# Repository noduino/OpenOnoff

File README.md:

Noduino Open Onoff
=======================================

[*Noduino Open Onoff (OpenOnoff V1.0)*](http://wiki.jackslab.org/Noduino_OpenOnoff)

[*Noduino Open Onoff (OpenOnoff V1.0)*](http://wiki.jackslab.org/Noduino_OpenOnoff)

Overview
-------------------

* AC 85V - 250V WiFi Smart Switch
* ESP8285 inside
* 250V 10A relay
* Shell size 63mm x 33mm x 21mm (H)

Shell
-------------------

* https://item.taobao.com/item.htm?id=535597515580

WiFi Module
-------------------

[*Noduino NodeC WiFi Module*](http://wiki.jackslab.org/Noduino_SmartNode)

SCH
-------------------

[*Noduino Open Onoff (OpenOnoff V1.0)*](http://wiki.jackslab.org/Noduino_OpenOnoff)

Layout
-------------------

[*Noduino Open Onoff (OpenOnoff V1.0)*](http://wiki.jackslab.org/Noduino_OpenOnoff)

WiKi
-------------------

* http://wiki.jackslab.org/Noduino_OpenOnoff

License Information
-------------------
The hardware is released under [Creative Commons ShareAlike 4.0 International](https://creativecommons.org/licenses/by-sa/4.0/).

Distributed as-is; no warranty is given.

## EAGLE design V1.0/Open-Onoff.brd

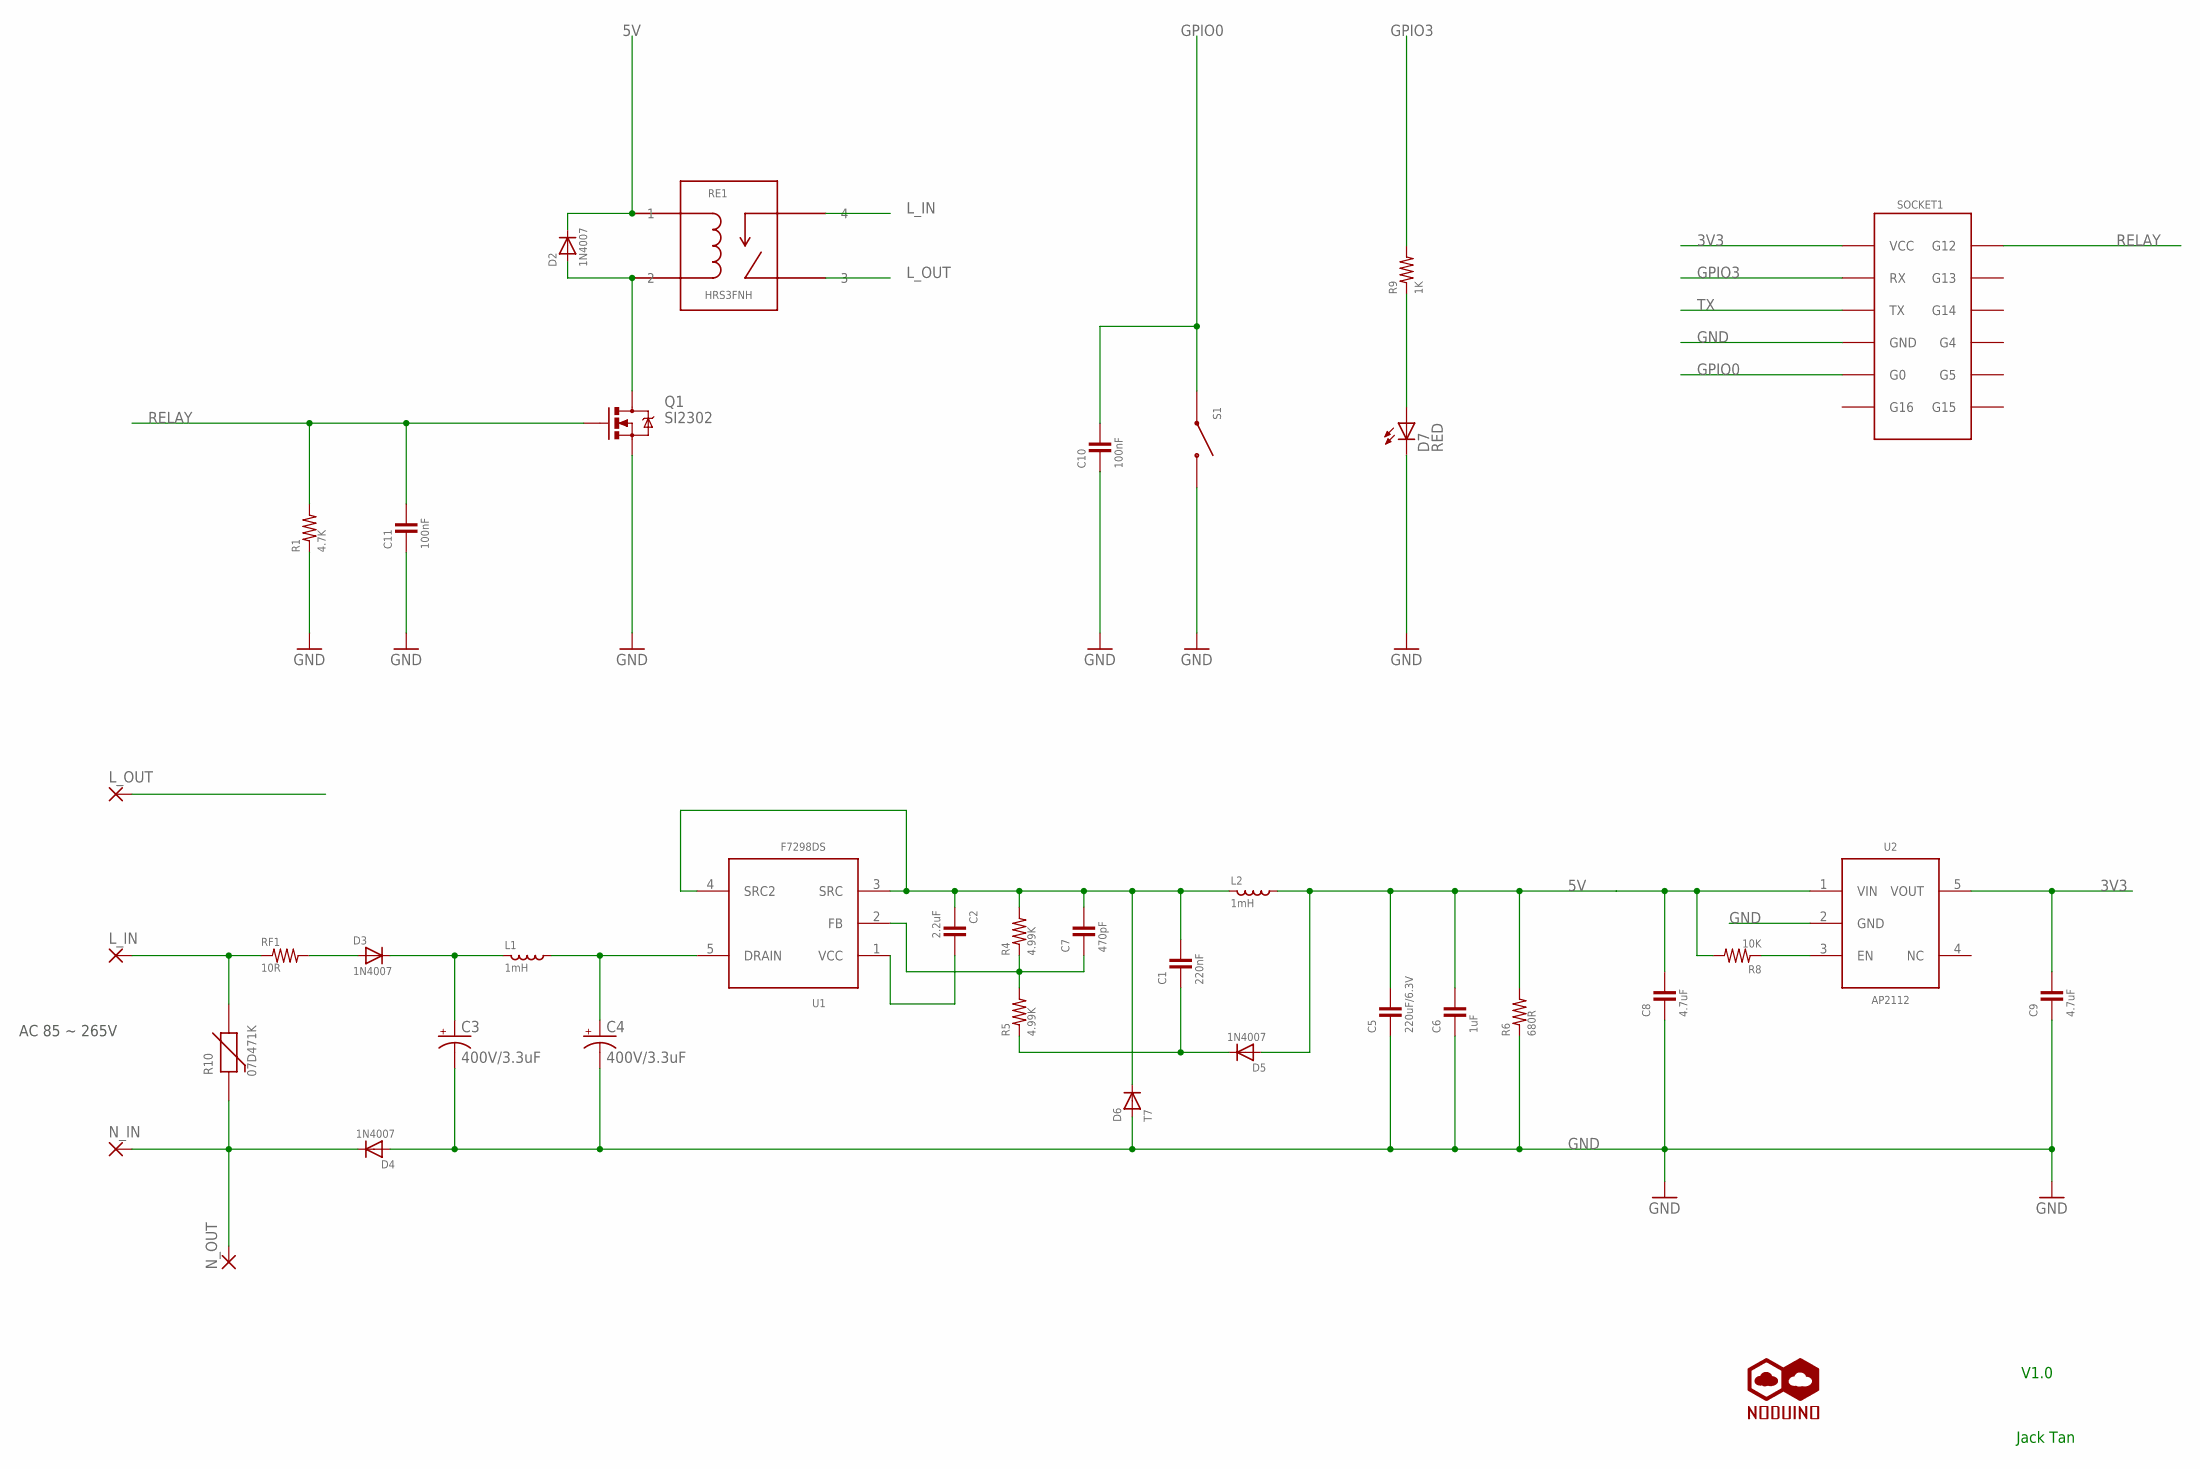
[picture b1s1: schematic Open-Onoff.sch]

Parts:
C1: 220nF; 0402-CAP
C2: 2.2uF; 0603-CAP
C3, C4: 400V/3.3uF; CPOL-RADIOA-3.3UF-400V
C5: 220uF/6.3V; B3528-CAP
C6: 1uF; 0402-CAP
C7: 470pF; 0402-CAP
C8, C9: 4.7uF; 0603-CAP
C10, C11: 100nF; 0402-CAP
D2: 1N4007; SOD-323
D3, D4, D5: 1N4007; 2.54-0.5
D6: T7; SOD-123
D7: RED; LED3MM
L1: 1mH; 2.54-0.5
L2: 1mH; INDUCTOR-5-0.5
L_IN: 2,15/1,0
L_OUT: 2,15/1,0
N_IN: 2,15/1,0
N_OUT: 2,15/1,0
Q1: SI2302; SOT23-3
R1: 4.7K; 0402-RES
R4, R5: 4.99K; 0402-RES
R6: 680R; 0402-RES
R8: 10K; 0603-RES
R9: 1K; 0402-RES
R10: 07D471K
RE1: HRS3FNH; HKE-HRS3FN
RF1: 10R; 2.54-0.5
S1: SWITCH-4DIPTS-037; SWITCH-TS-037
SOCKET1: MOD-SOCKET-V2.0; MOD-PLUG-SOCKET-V2.0
U1: F7298; SOT23-5
U2: AP2112; SOT23-5
U$1: NODUINO-LOGO-ALL; NODUINO-ALL-1

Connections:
3V3: C9.2, SOCKET1.1 (VCC), U2.5 (VOUT)
5V: C5.2, C6.2, C8.2, D2.1 (C), D5.P$1 (A), L2.P$2 (X2), R6.2, R8.2, RE1.1, U2.1 (VIN)
GND: C3.P$2 (-), C4.P$2 (-), C5.1, C6.1, C8.1, C9.1, C10.1, C11.1, D4.P$1 (A), D6.A, D7.K (C), Q1.2 (S), R1.1, R6.1, S1.P$1 (1), SOCKET1.4 (GND), U2.2 (GND)
GPIO0: C10.2, S1.P$3 (2), SOCKET1.5 (G0)
GPIO3: R9.2, SOCKET1.2 (RX)
L_IN: L_IN.1, R10.P$2 (2), RE1.4, RF1.P$1 (1)
L_OUT: L_OUT.1, RE1.3
N: D4.P$2 (C), N_IN.1, N_OUT.1, R10.P$1 (1)
unnamed: D2.2 (A), Q1.3 (D), RE1.2
unnamed: C3.P$1 (+), D3.P$2 (C), L1.P$1 (X1)
unnamed: C4.P$1 (+), L1.P$2 (X2), U1.5 (DRAIN)
unnamed: C1.2, C2.1, C7.2, D6.C, L2.P$1 (X1), R4.2, U1.3 (SRC), U1.4 (SRC2)
unnamed: D3.P$1 (A), RF1.P$2 (2)
unnamed: C2.2, U1.1 (VCC)
unnamed: C7.1, R4.1, R5.2, U1.2 (FB)
unnamed: C1.1, D5.P$2 (C), R5.1
unnamed: R8.1, U2.3 (EN)
unnamed: D7.A, R9.1
RELAY: C11.2, Q1.1 (G), R1.2, SOCKET1.12 (G12)
TX: SOCKET1.3 (TX)

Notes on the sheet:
Jack Tan
V1.0
AC 85 ~ 265V

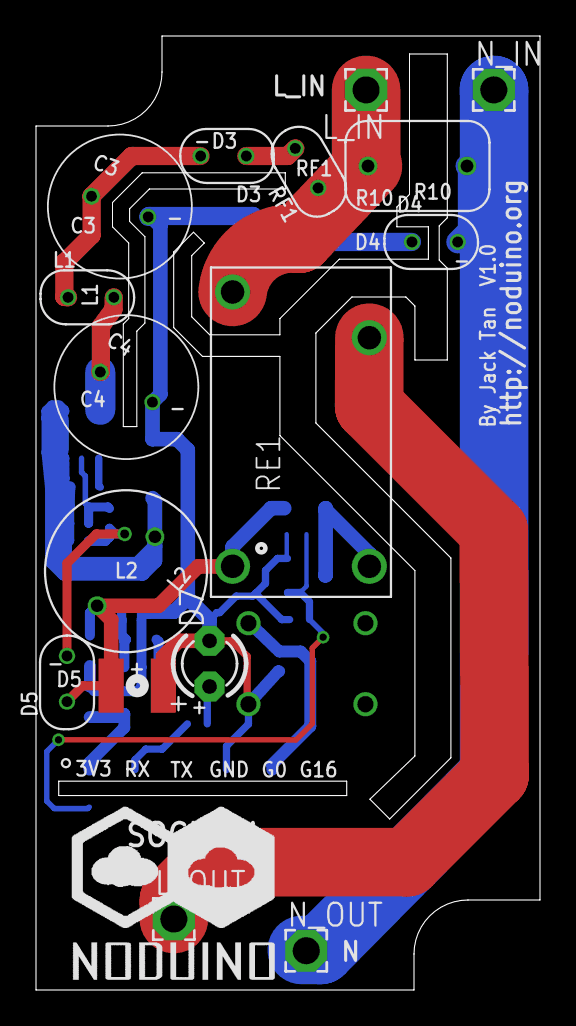
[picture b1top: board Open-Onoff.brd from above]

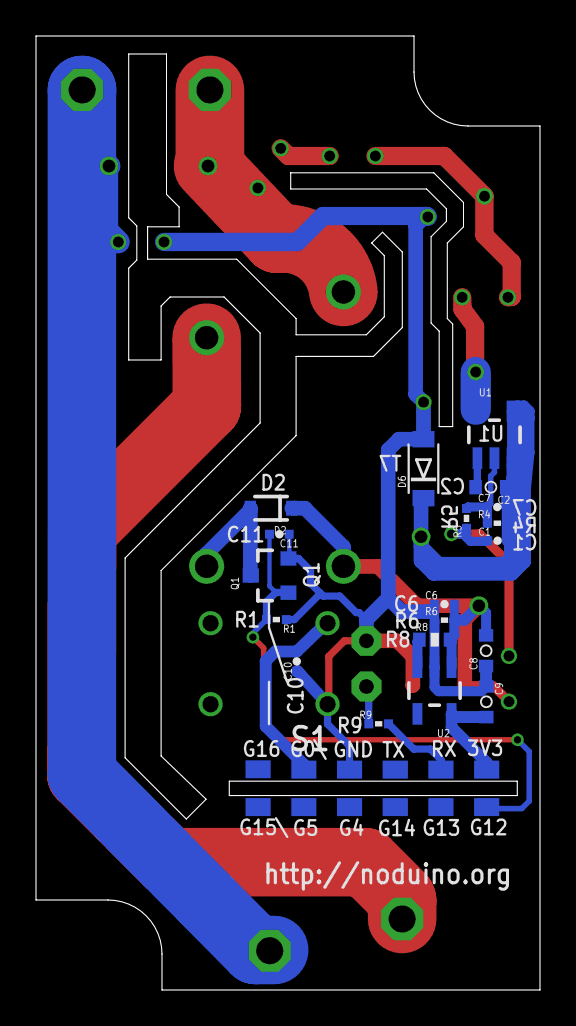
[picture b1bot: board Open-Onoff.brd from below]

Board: 2 copper layers, 28.0 x 53.0 mm, 38 parts (20 on the bottom side), 19 nets.

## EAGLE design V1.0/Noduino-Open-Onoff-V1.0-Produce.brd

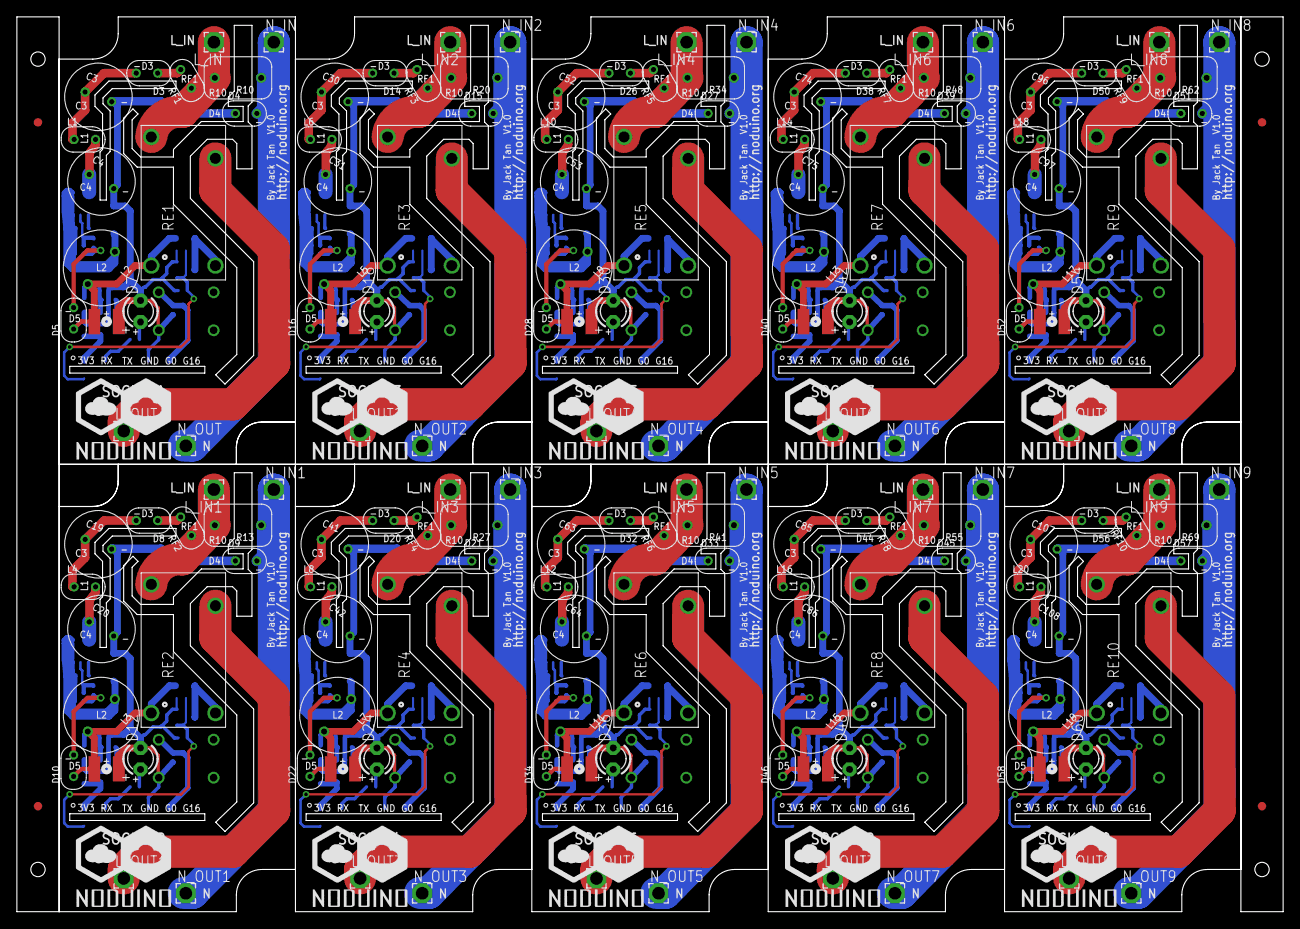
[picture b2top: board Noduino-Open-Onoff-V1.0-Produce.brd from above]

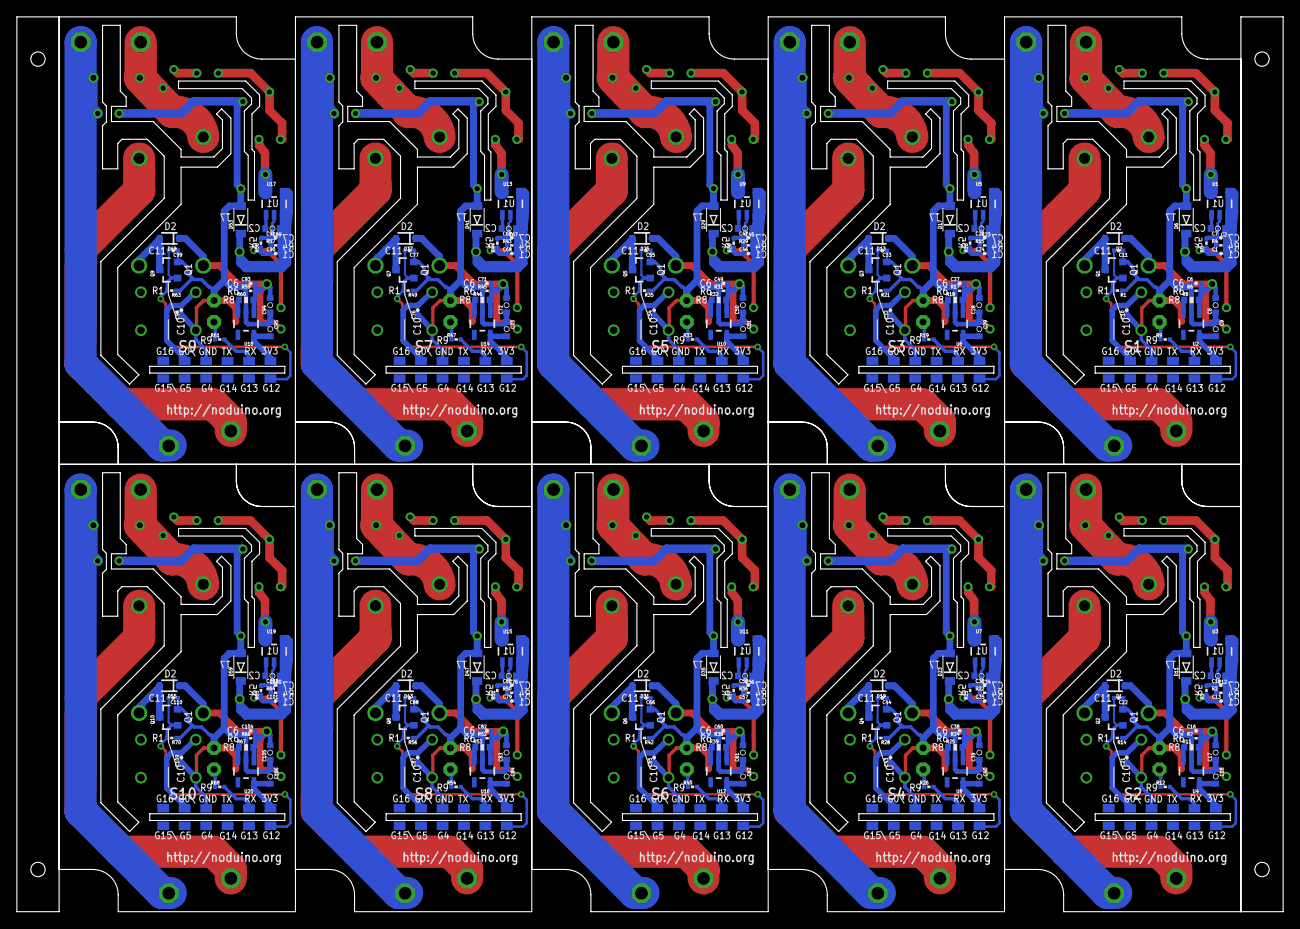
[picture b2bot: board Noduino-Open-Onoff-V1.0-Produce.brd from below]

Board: 2 copper layers, 150.0 x 106.0 mm, 384 parts (200 on the bottom side), 190 nets.

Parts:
C1, C13, C24, C35, C46, C57, C68, C79, C90, C101: 220nF; 0402-CAP
C2, C12, C23, C34, C45, C56, C67, C78, C89, C100: 2.2uF; 0603-CAP
C3, C4, C19, C20, C30, C31, C41, C42, C52, C53, C63, C64, C74, C75, C85, C86, C96, C97, C107, C108: 400V/3.3uF; CPOL-RADIOA-3.3UF-400V
C5, C15, C26, C37, C48, C59, C70, C81, C92, C103: 100uF/6.3V; B3528-CAP
C6, C16, C27, C38, C49, C60, C71, C82, C93, C104: 1uF; 0402-CAP
C7, C14, C25, C36, C47, C58, C69, C80, C91, C102: 470pF; 0402-CAP
C8, C9, C17, C18, C28, C29, C39, C40, C50, C51, C61, C62, C72, C73, C83, C84, C94, C95, C105, C106: 4.7uF; 0603-CAP
C10, C11, C21, C22, C32, C33, C43, C44, C54, C55, C65, C66, C76, C77, C87, C88, C98, C99, C109, C110: 100nF; 0402-CAP
D1, D2, D13, D19, D25, D31, D37, D43, D49, D55: 1N4007; SOD-323
D3, D4, D5, D8, D9, D10, D14, D15, D16, D20, D21, D22, D26, D27, D28, D32, D33, D34, D38, D39, D40, D44, D45, D46, D50, D51, D52, D56, D57, D58: 1N4007; 2.54-0.5
D6, D11, D17, D23, D29, D35, D41, D47, D53, D59: T7; SOD-123
D7, D12, D18, D24, D30, D36, D42, D48, D54, D60: RED; LED3MM
E$1, E$2, E$3, E$4: MARK-1MM
L1, L4, L6, L8, L10, L12, L14, L16, L18, L20: 1mH; 2.54-0.5
L2, L3, L5, L7, L9, L11, L13, L15, L17, L19: 1mH; INDUCTOR-5-0.5
L_IN, L_IN1, L_IN2, L_IN3, L_IN4, L_IN5, L_IN6, L_IN7, L_IN8, L_IN9: 2,15/1,0
L_OUT, L_OUT1, L_OUT2, L_OUT3, L_OUT4, L_OUT5, L_OUT6, L_OUT7, L_OUT8, L_OUT9: 2,15/1,0
N_IN, N_IN1, N_IN2, N_IN3, N_IN4, N_IN5, N_IN6, N_IN7, N_IN8, N_IN9: 2,15/1,0
N_OUT, N_OUT1, N_OUT2, N_OUT3, N_OUT4, N_OUT5, N_OUT6, N_OUT7, N_OUT8, N_OUT9: 2,15/1,0
Q1, Q2, Q3, Q4, Q5, Q6, Q7, Q8, Q9, Q10: SI2302; SOT23-3
R1, R9, R12, R14, R19, R21, R26, R28, R33, R35, R40, R42, R47, R49, R54, R56, R61, R63, R68, R70: 1K; 0402-RES
R2, R3, R4, R5, R15, R16, R22, R23, R29, R30, R36, R37, R43, R44, R50, R51, R57, R58, R64, R65: 4.99K; 0402-RES
R6, R7, R17, R24, R31, R38, R45, R52, R59, R66: 680R; 0402-RES
R8, R11, R18, R25, R32, R39, R46, R53, R60, R67: 10K; 0603-RES
R10, R13, R20, R27, R34, R41, R48, R55, R62, R69: 07D471K
RE1, RE2, RE3, RE4, RE5, RE6, RE7, RE8, RE9, RE10: HRS3FNH; HKE-HRS3FN
RF1, RF2, RF3, RF4, RF5, RF6, RF7, RF8, RF9, RF10: 10R; 2.54-0.5
S1, S2, S3, S4, S5, S6, S7, S8, S9, S10: SWITCH-TS-037
SOCKET1, SOCKET2, SOCKET3, SOCKET4, SOCKET5, SOCKET6, SOCKET7, SOCKET8, SOCKET9, SOCKET10: MOD-SOCKET-V2.0; MOD-PLUG-SOCKET-V2.0
U1, U3, U5, U7, U9, U11, U13, U15, U17, U19: F7298; SOT23-5
U2, U4, U6, U8, U10, U12, U14, U16, U18, U20: AP2112; SOT23-5
U$1, U$2, U$3, U$4, U$5, U$6, U$7, U$8, U$9, U$10: NODUINO-LOGO-ALL; NODUINO-ALL-1

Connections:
3V1: C18.2, SOCKET2.1, U4.5
3V2: C29.2, SOCKET3.1, U6.5
3V3: C9.2, SOCKET1.1, U2.5
3V4: C40.2, SOCKET4.1, U8.5
3V5: C51.2, SOCKET5.1, U10.5
3V6: C62.2, SOCKET6.1, U12.5
3V7: C73.2, SOCKET7.1, U14.5
3V8: C84.2, SOCKET8.1, U16.5
3V9: C95.2, SOCKET9.1, U18.5
3V10: C106.2, SOCKET10.1, U20.5
5V: C5.2, C6.2, C8.2, D2.1, D5.P$1, L2.P$2, R6.2, R8.2, RE1.1, U2.1
5V1: C15.2, C16.2, C17.2, D1.1, D10.P$1, L3.P$2, R7.2, R11.2, RE2.1, U4.1
5V2: C26.2, C27.2, C28.2, D13.1, D16.P$1, L5.P$2, R17.2, R18.2, RE3.1, U6.1
5V3: C37.2, C38.2, C39.2, D19.1, D22.P$1, L7.P$2, R24.2, R25.2, RE4.1, U8.1
5V4: C48.2, C49.2, C50.2, D25.1, D28.P$1, L9.P$2, R31.2, R32.2, RE5.1, U10.1
5V5: C59.2, C60.2, C61.2, D31.1, D34.P$1, L11.P$2, R38.2, R39.2, RE6.1, U12.1
5V6: C70.2, C71.2, C72.2, D37.1, D40.P$1, L13.P$2, R45.2, R46.2, RE7.1, U14.1
5V7: C81.2, C82.2, C83.2, D43.1, D46.P$1, L15.P$2, R52.2, R53.2, RE8.1, U16.1
5V8: C92.2, C93.2, C94.2, D49.1, D52.P$1, L17.P$2, R59.2, R60.2, RE9.1, U18.1
5V9: C103.2, C104.2, C105.2, D55.1, D58.P$1, L19.P$2, R66.2, R67.2, RE10.1, U20.1
GND: C3.P$2, C4.P$2, C5.1, C6.1, C8.1, C9.1, C10.1, C11.1, D4.P$1, D6.A, D7.K, Q1.2, R1.1, R6.1, S1.P$1, SOCKET1.4, U2.2
GND1: C15.1, C16.1, C17.1, C18.1, C19.P$2, C20.P$2, C21.1, C22.1, D9.P$1, D11.A, D12.K, Q2.2, R7.1, R14.1, S2.P$1, SOCKET2.4, U4.2
GND2: C26.1, C27.1, C28.1, C29.1, C30.P$2, C31.P$2, C32.1, C33.1, D15.P$1, D17.A, D18.K, Q3.2, R17.1, R21.1, S3.P$1, SOCKET3.4, U6.2
GND3: C37.1, C38.1, C39.1, C40.1, C41.P$2, C42.P$2, C43.1, C44.1, D21.P$1, D23.A, D24.K, Q4.2, R24.1, R28.1, S4.P$1, SOCKET4.4, U8.2
GND4: C48.1, C49.1, C50.1, C51.1, C52.P$2, C53.P$2, C54.1, C55.1, D27.P$1, D29.A, D30.K, Q5.2, R31.1, R35.1, S5.P$1, SOCKET5.4, U10.2
GND5: C59.1, C60.1, C61.1, C62.1, C63.P$2, C64.P$2, C65.1, C66.1, D33.P$1, D35.A, D36.K, Q6.2, R38.1, R42.1, S6.P$1, SOCKET6.4, U12.2
GND6: C70.1, C71.1, C72.1, C73.1, C74.P$2, C75.P$2, C76.1, C77.1, D39.P$1, D41.A, D42.K, Q7.2, R45.1, R49.1, S7.P$1, SOCKET7.4, U14.2
GND7: C81.1, C82.1, C83.1, C84.1, C85.P$2, C86.P$2, C87.1, C88.1, D45.P$1, D47.A, D48.K, Q8.2, R52.1, R56.1, S8.P$1, SOCKET8.4, U16.2
GND8: C92.1, C93.1, C94.1, C95.1, C96.P$2, C97.P$2, C98.1, C99.1, D51.P$1, D53.A, D54.K, Q9.2, R59.1, R63.1, S9.P$1, SOCKET9.4, U18.2
GND9: C103.1, C104.1, C105.1, C106.1, C107.P$2, C108.P$2, C109.1, C110.1, D57.P$1, D59.A, D60.K, Q10.2, R66.1, R70.1, S10.P$1, SOCKET10.4, U20.2
GPIO0: C10.2, S1.P$3, SOCKET1.5
GPIO1: R12.2, SOCKET2.2
GPIO2: C21.2, S2.P$3, SOCKET2.5
GPIO3: R9.2, SOCKET1.2
GPIO4: R19.2, SOCKET3.2
GPIO5: C32.2, S3.P$3, SOCKET3.5
GPIO6: R26.2, SOCKET4.2
GPIO7: C43.2, S4.P$3, SOCKET4.5
GPIO8: R33.2, SOCKET5.2
GPIO9: C54.2, S5.P$3, SOCKET5.5
GPIO10: R40.2, SOCKET6.2
GPIO11: C65.2, S6.P$3, SOCKET6.5
GPIO12: R47.2, SOCKET7.2
GPIO13: C76.2, S7.P$3, SOCKET7.5
GPIO14: R54.2, SOCKET8.2
GPIO15: C87.2, S8.P$3, SOCKET8.5
GPIO16: R61.2, SOCKET9.2
GPIO17: C98.2, S9.P$3, SOCKET9.5
GPIO18: R68.2, SOCKET10.2
GPIO19: C109.2, S10.P$3, SOCKET10.5
L_IN: L_IN.1, R10.P$2, RE1.4, RF1.P$1
L_IN1: L_IN1.1, R13.P$2, RE2.4, RF2.P$1
L_IN2: L_IN2.1, R20.P$2, RE3.4, RF3.P$1
L_IN3: L_IN3.1, R27.P$2, RE4.4, RF4.P$1
L_IN4: L_IN4.1, R34.P$2, RE5.4, RF5.P$1
L_IN5: L_IN5.1, R41.P$2, RE6.4, RF6.P$1
L_IN6: L_IN6.1, R48.P$2, RE7.4, RF7.P$1
L_IN7: L_IN7.1, R55.P$2, RE8.4, RF8.P$1
L_IN8: L_IN8.1, R62.P$2, RE9.4, RF9.P$1
L_IN9: L_IN9.1, R69.P$2, RE10.4, RF10.P$1
L_OUT: L_OUT.1, RE1.3
L_OUT1: L_OUT1.1, RE2.3
L_OUT2: L_OUT2.1, RE3.3
L_OUT3: L_OUT3.1, RE4.3
L_OUT4: L_OUT4.1, RE5.3
L_OUT5: L_OUT5.1, RE6.3
L_OUT6: L_OUT6.1, RE7.3
L_OUT7: L_OUT7.1, RE8.3
L_OUT8: L_OUT8.1, RE9.3
L_OUT9: L_OUT9.1, RE10.3
N: D4.P$2, N_IN.1, N_OUT.1, R10.P$1
N1: D9.P$2, N_IN1.1, N_OUT1.1, R13.P$1
N2: D15.P$2, N_IN2.1, N_OUT2.1, R20.P$1
N3: D21.P$2, N_IN3.1, N_OUT3.1, R27.P$1
N4: D27.P$2, N_IN4.1, N_OUT4.1, R34.P$1
N5: D33.P$2, N_IN5.1, N_OUT5.1, R41.P$1
N6: D39.P$2, N_IN6.1, N_OUT6.1, R48.P$1
N7: D45.P$2, N_IN7.1, N_OUT7.1, R55.P$1
N8: D51.P$2, N_IN8.1, N_OUT8.1, R62.P$1
N9: D57.P$2, N_IN9.1, N_OUT9.1, R69.P$1
unnamed: D1.2, Q2.3, RE2.2
unnamed: D2.2, Q1.3, RE1.2
unnamed: C3.P$1, D3.P$2, L1.P$1
unnamed: C19.P$1, D8.P$2, L4.P$1
unnamed: C4.P$1, L1.P$2, U1.5
unnamed: C1.2, C2.1, C7.2, D6.C, L2.P$1, R4.2, U1.3, U1.4
unnamed: D3.P$1, RF1.P$2
unnamed: C20.P$1, L4.P$2, U3.5
unnamed: C12.1, C13.2, C14.2, D11.C, L3.P$1, R2.2, U3.3, U3.4
unnamed: C2.2, U1.1
unnamed: C7.1, R4.1, R5.2, U1.2
unnamed: C1.1, D5.P$2, R5.1
unnamed: R8.1, U2.3
unnamed: D7.A, R9.1
unnamed: D8.P$1, RF2.P$2
unnamed: C12.2, U3.1
unnamed: C14.1, R2.1, R3.2, U3.2
unnamed: C13.1, D10.P$2, R3.1
unnamed: R11.1, U4.3
unnamed: D12.A, R12.1
unnamed: D13.2, Q3.3, RE3.2
unnamed: C30.P$1, D14.P$2, L6.P$1
unnamed: C31.P$1, L6.P$2, U5.5
unnamed: C23.1, C24.2, C25.2, D17.C, L5.P$1, R15.2, U5.3, U5.4
unnamed: D14.P$1, RF3.P$2
unnamed: C23.2, U5.1
unnamed: C25.1, R15.1, R16.2, U5.2
unnamed: C24.1, D16.P$2, R16.1
unnamed: R18.1, U6.3
unnamed: D18.A, R19.1
unnamed: D19.2, Q4.3, RE4.2
unnamed: C41.P$1, D20.P$2, L8.P$1
unnamed: C42.P$1, L8.P$2, U7.5
unnamed: C34.1, C35.2, C36.2, D23.C, L7.P$1, R22.2, U7.3, U7.4
unnamed: D20.P$1, RF4.P$2
unnamed: C34.2, U7.1
unnamed: C36.1, R22.1, R23.2, U7.2
unnamed: C35.1, D22.P$2, R23.1
unnamed: R25.1, U8.3
unnamed: D24.A, R26.1
unnamed: D25.2, Q5.3, RE5.2
unnamed: C52.P$1, D26.P$2, L10.P$1
unnamed: C53.P$1, L10.P$2, U9.5
unnamed: C45.1, C46.2, C47.2, D29.C, L9.P$1, R29.2, U9.3, U9.4
unnamed: D26.P$1, RF5.P$2
unnamed: C45.2, U9.1
unnamed: C47.1, R29.1, R30.2, U9.2
unnamed: C46.1, D28.P$2, R30.1
unnamed: R32.1, U10.3
unnamed: D30.A, R33.1
unnamed: D31.2, Q6.3, RE6.2
unnamed: C63.P$1, D32.P$2, L12.P$1
unnamed: C64.P$1, L12.P$2, U11.5
unnamed: C56.1, C57.2, C58.2, D35.C, L11.P$1, R36.2, U11.3, U11.4
unnamed: D32.P$1, RF6.P$2
unnamed: C56.2, U11.1
unnamed: C58.1, R36.1, R37.2, U11.2
unnamed: C57.1, D34.P$2, R37.1
unnamed: R39.1, U12.3
unnamed: D36.A, R40.1
unnamed: D37.2, Q7.3, RE7.2
unnamed: C74.P$1, D38.P$2, L14.P$1
unnamed: C75.P$1, L14.P$2, U13.5
unnamed: C67.1, C68.2, C69.2, D41.C, L13.P$1, R43.2, U13.3, U13.4
unnamed: D38.P$1, RF7.P$2
unnamed: C67.2, U13.1
unnamed: C69.1, R43.1, R44.2, U13.2
unnamed: C68.1, D40.P$2, R44.1
unnamed: R46.1, U14.3
unnamed: D42.A, R47.1
unnamed: D43.2, Q8.3, RE8.2
unnamed: C85.P$1, D44.P$2, L16.P$1
unnamed: C86.P$1, L16.P$2, U15.5
unnamed: C78.1, C79.2, C80.2, D47.C, L15.P$1, R50.2, U15.3, U15.4
unnamed: D44.P$1, RF8.P$2
unnamed: C78.2, U15.1
unnamed: C80.1, R50.1, R51.2, U15.2
unnamed: C79.1, D46.P$2, R51.1
unnamed: R53.1, U16.3
unnamed: D48.A, R54.1
unnamed: D49.2, Q9.3, RE9.2
unnamed: C96.P$1, D50.P$2, L18.P$1
unnamed: C97.P$1, L18.P$2, U17.5
unnamed: C89.1, C90.2, C91.2, D53.C, L17.P$1, R57.2, U17.3, U17.4
unnamed: D50.P$1, RF9.P$2
unnamed: C89.2, U17.1
unnamed: C91.1, R57.1, R58.2, U17.2
unnamed: C90.1, D52.P$2, R58.1
unnamed: R60.1, U18.3
unnamed: D54.A, R61.1
unnamed: D55.2, Q10.3, RE10.2
unnamed: C107.P$1, D56.P$2, L20.P$1
unnamed: C108.P$1, L20.P$2, U19.5
unnamed: C100.1, C101.2, C102.2, D59.C, L19.P$1, R64.2, U19.3, U19.4
unnamed: D56.P$1, RF10.P$2
unnamed: C100.2, U19.1
unnamed: C102.1, R64.1, R65.2, U19.2
unnamed: C101.1, D58.P$2, R65.1
unnamed: R67.1, U20.3
unnamed: D60.A, R68.1
RELAY: C11.2, Q1.1, R1.2, SOCKET1.12
RELAY1: C22.2, Q2.1, R14.2, SOCKET2.12
RELAY2: C33.2, Q3.1, R21.2, SOCKET3.12
RELAY3: C44.2, Q4.1, R28.2, SOCKET4.12
RELAY4: C55.2, Q5.1, R35.2, SOCKET5.12
RELAY5: C66.2, Q6.1, R42.2, SOCKET6.12
RELAY6: C77.2, Q7.1, R49.2, SOCKET7.12
RELAY7: C88.2, Q8.1, R56.2, SOCKET8.12
RELAY8: C99.2, Q9.1, R63.2, SOCKET9.12
RELAY9: C110.2, Q10.1, R70.2, SOCKET10.12

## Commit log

2019-04-23 add the pcb design files
2019-04-23 add the readme
2019-04-23 update the readme
